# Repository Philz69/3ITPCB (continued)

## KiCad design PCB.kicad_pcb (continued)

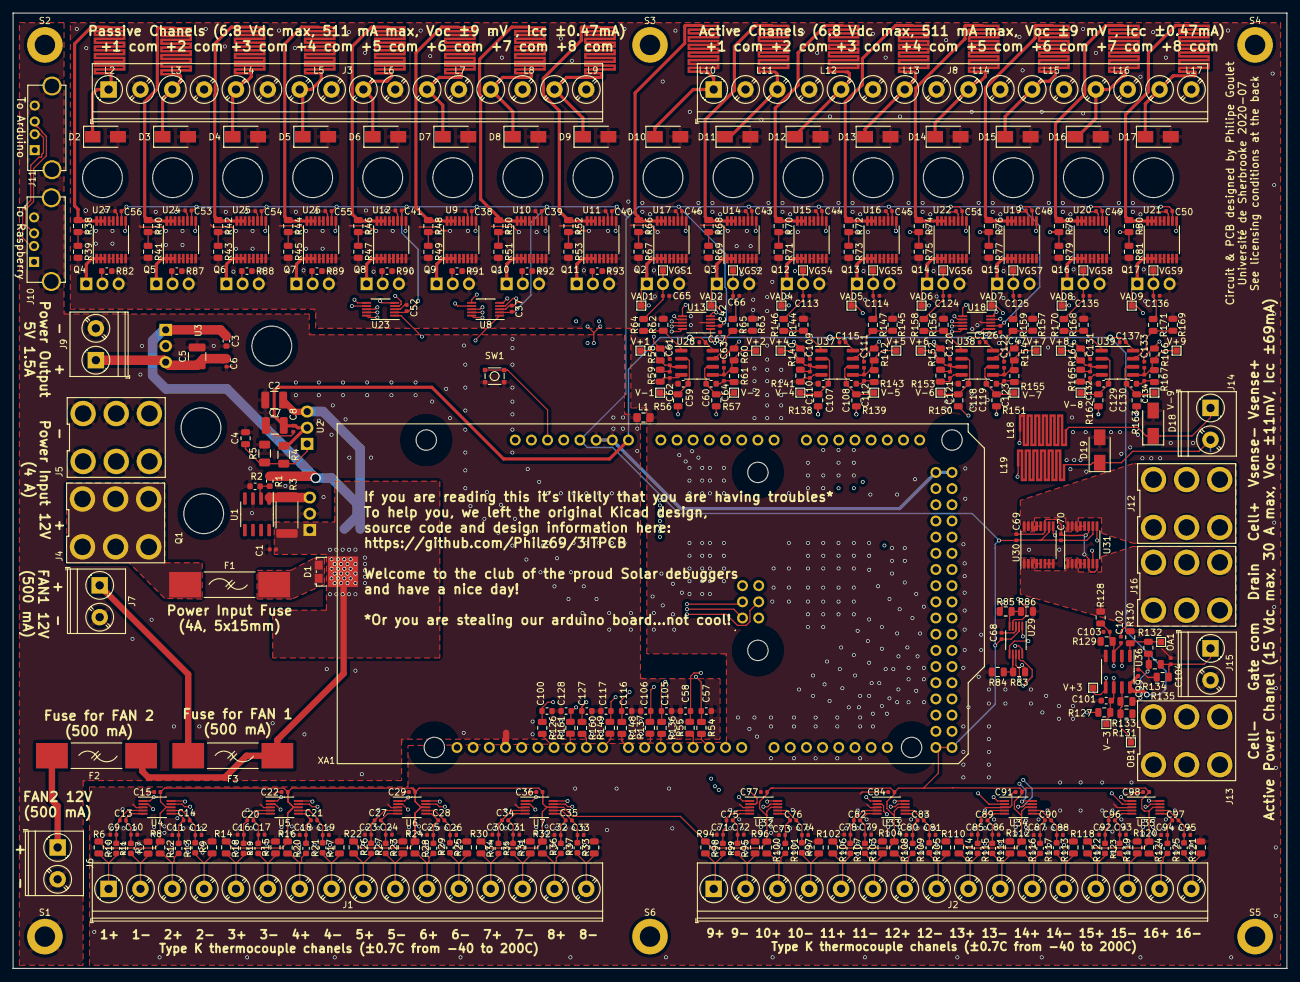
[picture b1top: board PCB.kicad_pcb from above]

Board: 4 copper layers, 200.0 x 150.0 mm, 465 parts (0 on the bottom side), 286 nets.

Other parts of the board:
C68, C69, C70: 0.1uF; C_0402_1005Metric
R83, R85: 100k; R_0805_2012Metric
R84, R86: 43k; R_0805_2012Metric
U29: ADC124S021CIMM_NOPB; VSSOP-10_3x3mm_P0.5mm
U30, U31: INA250A1PW; TSSOP-16_4.4x5mm_P0.65mm

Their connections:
/+5V: C68.1, C69.1, C70.1, U29.2, U30.10, U31.10; also elsewhere on the board
/Acquisition100W/CurrentSense20A1/OUT: U29.6, U31.9
/Acquisition100W/Voltage100W1/Vout: R83.2, R84.1, U29.7
/Acquisition100W/sheet5F05B519/Vout: R85.2, R86.1, U29.5
/CS13: U29.1; also elsewhere on the board
/MISO: U29.9; also elsewhere on the board
/MOSI: U29.8; also elsewhere on the board
/SCK: U29.10; also elsewhere on the board
/V+Sense100W: R85.1; also elsewhere on the board
/V-Sense100W: U29.4; also elsewhere on the board
/VinActif100W: R83.1, U30.14, U30.15, U30.16, U31.14, U31.15, U31.16; also elsewhere on the board
/VoutActif100W: U30.1, U30.2, U30.3, U31.1, U31.2, U31.3; also elsewhere on the board
GNDA: C68.2, C69.2, C70.2, R84.2, R86.2, U29.3, U30.6, U30.7, U30.8, U30.11, U31.6, U31.8, U31.11; also elsewhere on the board
unnamed: U30.4, U30.5
unnamed: U30.9, U31.7
unnamed: U30.12, U30.13
unnamed: U31.4, U31.5
unnamed: U31.12, U31.13

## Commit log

2020-06-18 commit initial
2020-06-18 Placement des cannaux de temperature
2020-06-18 Placement canal passif intial
2020-06-18 Placement canal passif
2020-06-18 Placement canal actif sauf charge active
2020-06-18 Placement première charge active
2020-06-18 Placement première charge active 2nd try
2020-06-18 Placement première charge active, pret a dupliquer
2020-06-18 Charge actives dupliques, placement filtres rc
2020-06-18 Placement Charge active 100w et filtres PWM
2020-06-19 Small modifications
2020-06-19 Defi releve!
2020-06-19 Essais de commiter tout les fichiers ce coup là
2020-06-20 Test placements
2020-06-20 Placement current sensors avec pads
2020-06-20 Placement charge active fini
2020-06-20 Petit ajustement pour accomoder le usb du arduino, pret pour routing
2020-06-20 Ajustement resistors température pour routing
2020-06-23 Debug routing
2020-06-24 Routing initial température
2020-06-24 retrait des test points inutiles
2020-06-24 routing temperature sauf chip select
2020-06-24 routing 5V temperature + routing initial canal 100w
2020-07-01 Routed most of the power
2020-07-01 More power routing
2020-07-02 Routing power termine, premiere version
2020-07-02 Ajout routing 5V manquant sur un dac
2020-07-02 routing usb
2020-07-02 routing chip select temprature
2020-07-03 derniere modifications
2020-07-05 Debut rerouting power sur face arriere
2020-07-05 Progres rerouting power
2020-07-05 Debut routing cannaux passifs
2020-07-06 Routing canaux passif presque terminé
2020-07-06 debut routing cannaux actifs
2020-07-07 Ajustement placement canaux actifs
2020-07-07 Placement cannaux actifs + debut routing pwm
2020-07-07 placement auto
2020-07-07 Routing canaux actifs + routing PWM 1-8 termine
2020-07-07 Routing PWM 9
2020-07-07 Routing canaux actifs
2020-07-08 simplification routing cannaux passifs
2020-07-08 routing entree analogiques
2020-07-08 Cleanup routing power + ajouts routing canal actif 100w
2020-07-08 routing input canaux voltages
2020-07-08 Ajout premiers via pour ground
2020-07-08 Ajout vias pour ground
2020-07-09 Rerouting SPI pour canaux temperature
2020-07-13 Changement pin pour switchs cannaux passifs
2020-07-15 Added info on silkscreen layers, fixed DRC problems, added a license
2020-07-17 Changement valeur de capaciteur + cleanup minime
2020-07-22 Version Envoyée pour fabrication
    Modifications de certaines traces pour accomoder le fait que le fournisseur ne peut pas faire un board avec 0.2 mm de spacing en 2 Oz ... on élargit les traces et on places des ouvertures dans le sol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
